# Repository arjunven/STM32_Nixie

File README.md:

# STM32 and USB-C Based Nixie Clock
A [Nixie](http://en.wikipedia.org/wiki/Nixie_tube) clock that's powered by USB-C and based on a STM32 microcontroller. Designed schematic, layout, and firmware from scratch! Fun mix of retro tech with modern electronics. Main Features:
  - Custom 5V to 180V boost converter that operates in discontinous conduction mode to power the Nixie tubes
  - USB-C Power input + bootloader
  - Push button dial that's used to set time and interface with the menu
  - Used high voltage shift registers to run the tube display
  - STM32F100 micro controller with abysmal flash storage ... because that's all that was in stock during the great covid parts shortage of 2021 when I started this project 

## Mostly Finished Product

  - Still would like to add a walnut enclosure and a nice wodden knob for the push button dial
  - 80/20 rule in full force

## Layout

- 4 Layer board

## Schematics
### 5V to 180V Boost Converter

### Full Schematics
[Full Schematics here
](https://github.com/arjunven/STM32_Nixie/blob/main/pcb/outputs/STM32_Nixie_Schematics.pdf
)

## Bringup/Development

- Bring up of HV shift register driver with assistance from Merlin

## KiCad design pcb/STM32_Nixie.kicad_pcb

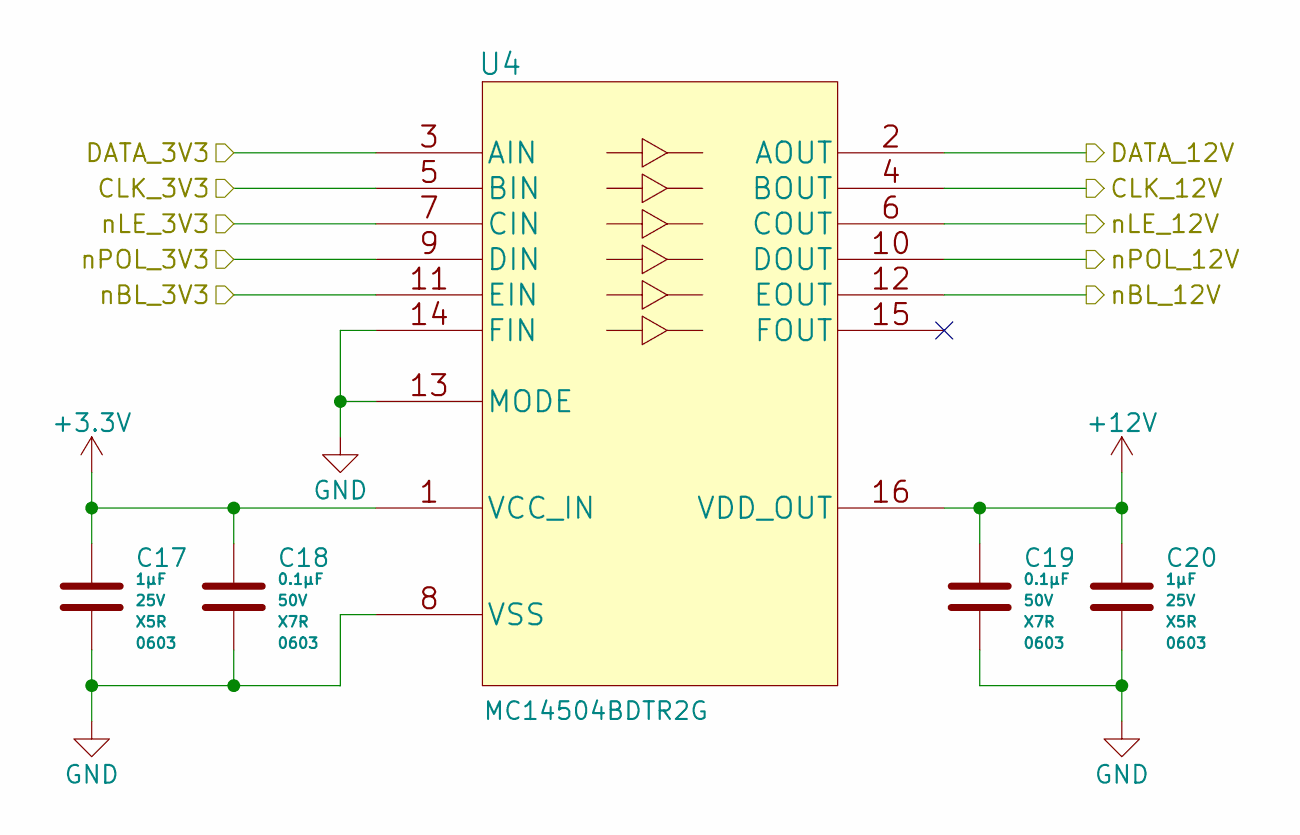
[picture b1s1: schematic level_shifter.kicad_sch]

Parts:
C17, C20: CAP_CER_1u_25V_X5R_0603; C_0603_1608Metric; Voltage 25V; ManufacturerPN CC0603KRX5R8BB105
C18, C19: CAP_CER_0u1_50V_X7R_0603; C_0603_1608Metric; Voltage 50V; ManufacturerPN CL10B104KB8NNNC
U4: IC_LVL_ONSEMI_MC14504BDTR2G; MC14504BDTR2G; ManufacturerPN MC14504BDTR2G

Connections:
+3.3V: C17.1, C18.1, U4.1 (VCC_IN); also elsewhere on the board
+12V: C19.1, C20.1, U4.16 (VDD_OUT); also elsewhere on the board
/PWM_nBL_3V3: U4.11 (EIN); also elsewhere on the board
/PWM_nBL_12V: U4.12 (EOUT); also elsewhere on the board
/SPI_PICO_3V3: U4.3 (AIN); also elsewhere on the board
/SPI_PICO_12V: U4.2 (AOUT); also elsewhere on the board
/SPI_SCK_3V3: U4.5 (BIN); also elsewhere on the board
/SPI_SCK_12V: U4.4 (BOUT); also elsewhere on the board
/SPI_nCS_nLE_3V3: U4.7 (CIN); also elsewhere on the board
/SPI_nCS_nLE_12V: U4.6 (COUT); also elsewhere on the board
/nPOL_3V3: U4.9 (DIN); also elsewhere on the board
/nPOL_12V: U4.10 (DOUT); also elsewhere on the board
GND: C17.2, C18.2, C19.2, C20.2, U4.8 (VSS), U4.13 (MODE), U4.14 (FIN); also elsewhere on the board

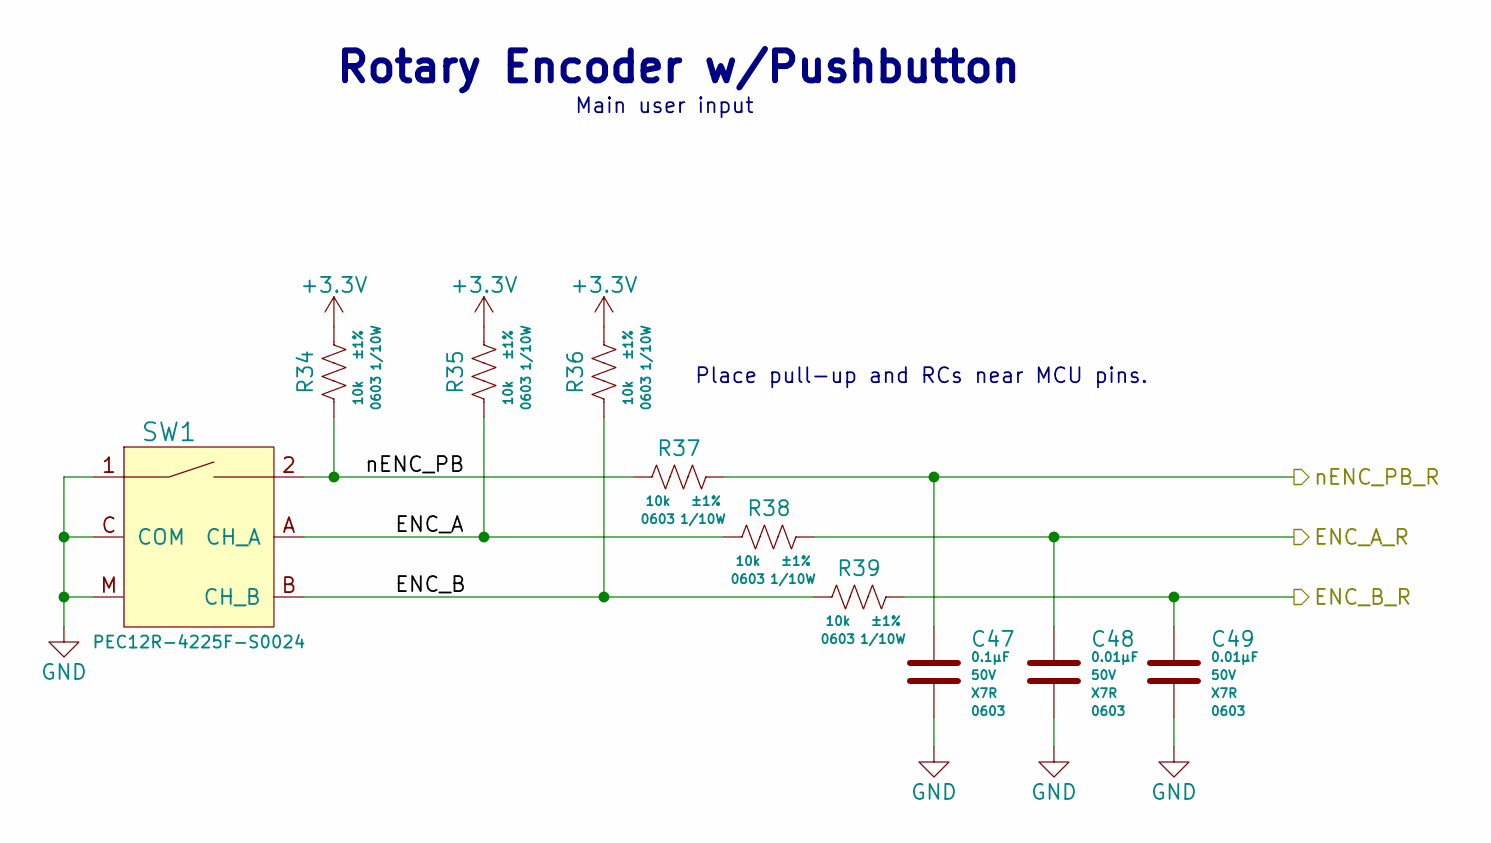
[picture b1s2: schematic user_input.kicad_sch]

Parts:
C47: CAP_CER_0u1_50V_X7R_0603; C_0603_1608Metric; Voltage 50V; ManufacturerPN CL10B104KB8NNNC
C48, C49: CAP_CER_0u01_50V_X7R_0603; C_0603_1608Metric; Voltage 50V; ManufacturerPN CL10B103KB8NNNC
R34, R35, R36, R37, R38, R39: RES_10K_1P_1/10W_0603; R_0603_1608Metric; Tolerance ±1%; ManufacturerPN RC0603FR-0710KL
SW1: ENC_SPST_24PPR_PEC12R-4225F-S0024; ENC_SPST_PEC12R-4x25F-Sxxx; ManufacturerPN PEC12R-4225F-S0024

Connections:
+3.3V: R34.1, R35.1, R36.1; also elsewhere on the board
/MCU/ENC_A_R: C48.1, R38.1; also elsewhere on the board
/MCU/ENC_B_R: C49.1, R39.1; also elsewhere on the board
/MCU/nENC_PB_R: C47.1, R37.1; also elsewhere on the board
/User Input/ENC_A: R35.2, R38.2, SW1.A (CH_A)
/User Input/ENC_B: R36.2, R39.2, SW1.B (CH_B)
/User Input/nENC_PB: R34.2, R37.2, SW1.2
GND: C47.2, C48.2, C49.2, SW1.1, SW1.C (COM), SW1.M; also elsewhere on the board

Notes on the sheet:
Place pull-up and RCs near MCU pins.
Rotary Encoder w/Pushbutton
Main user input

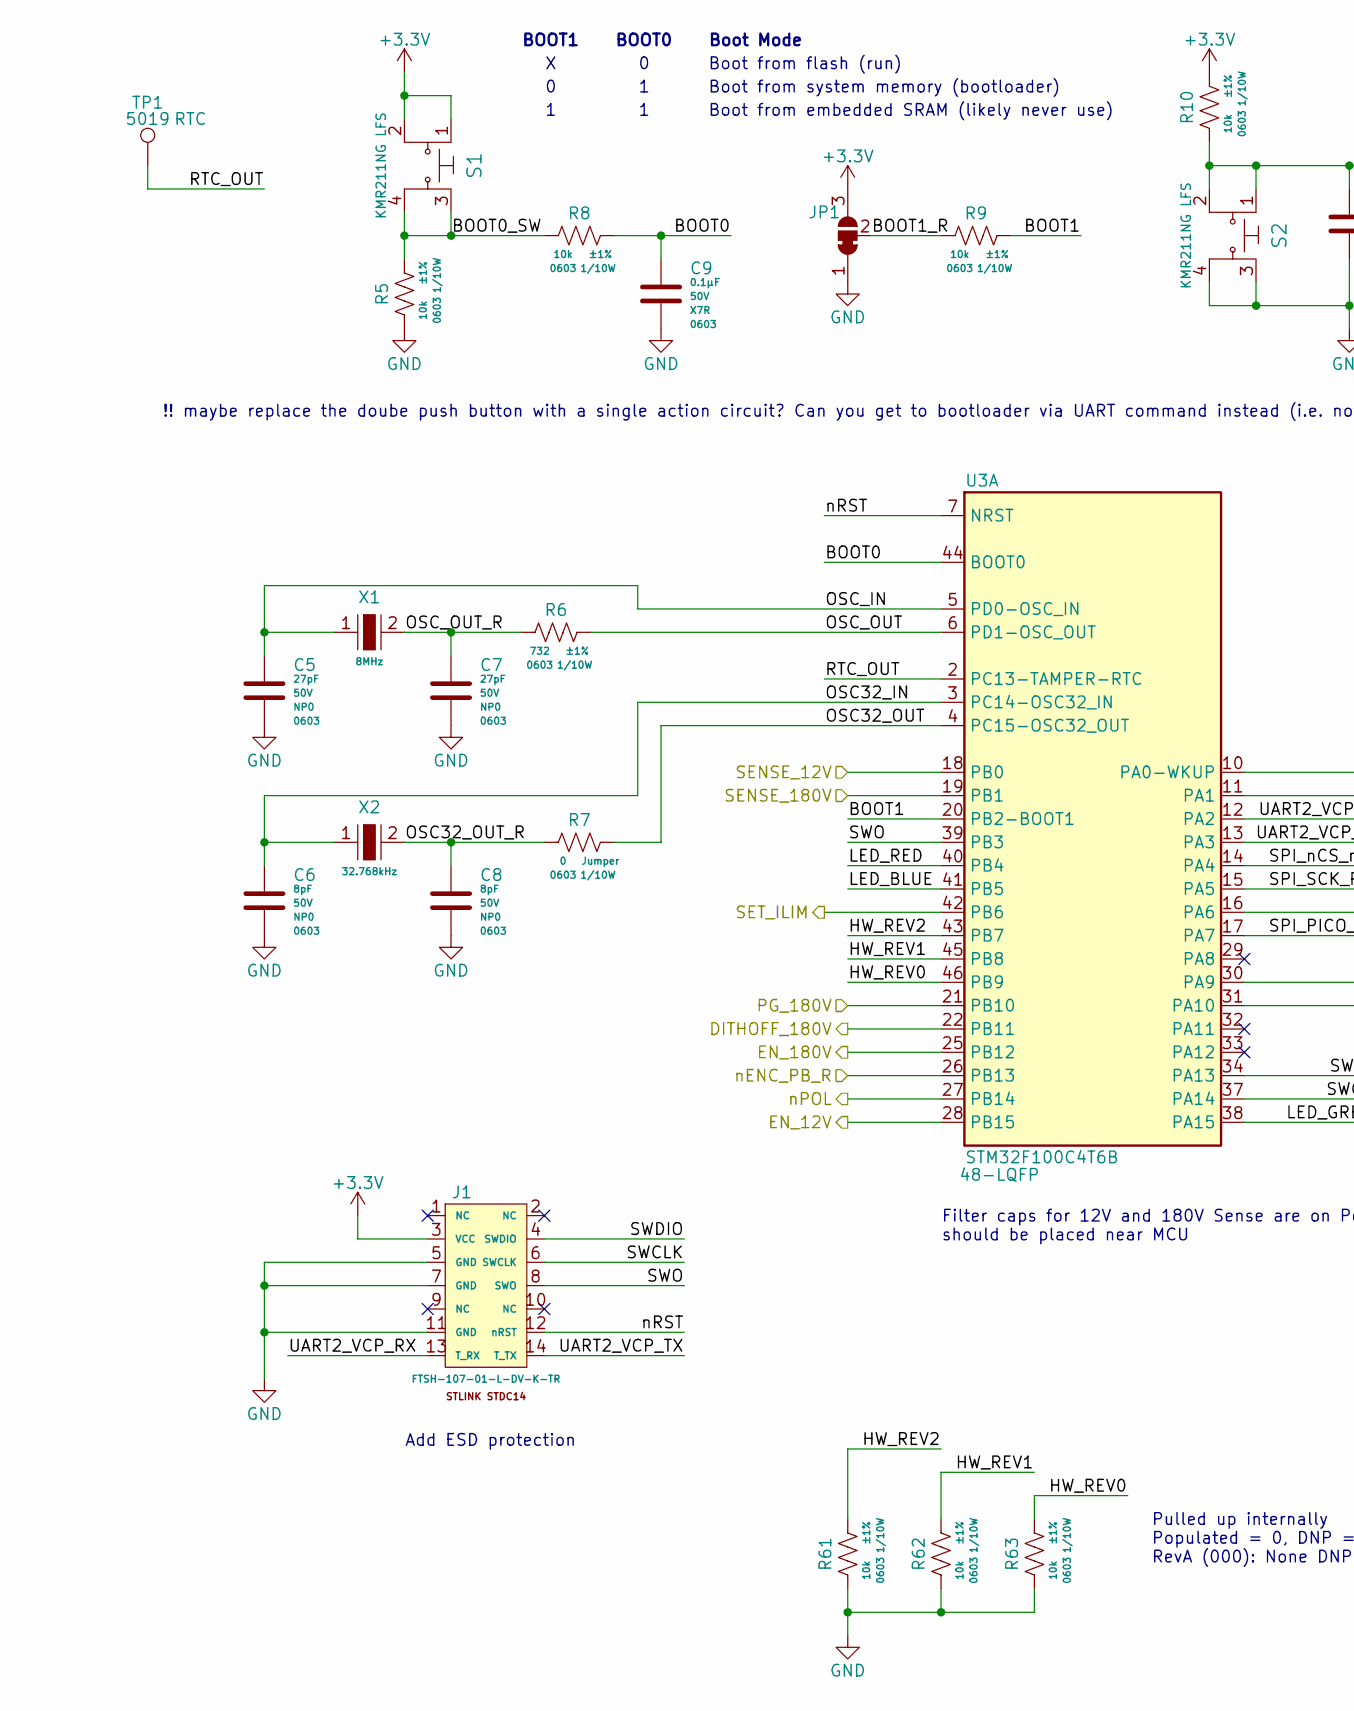
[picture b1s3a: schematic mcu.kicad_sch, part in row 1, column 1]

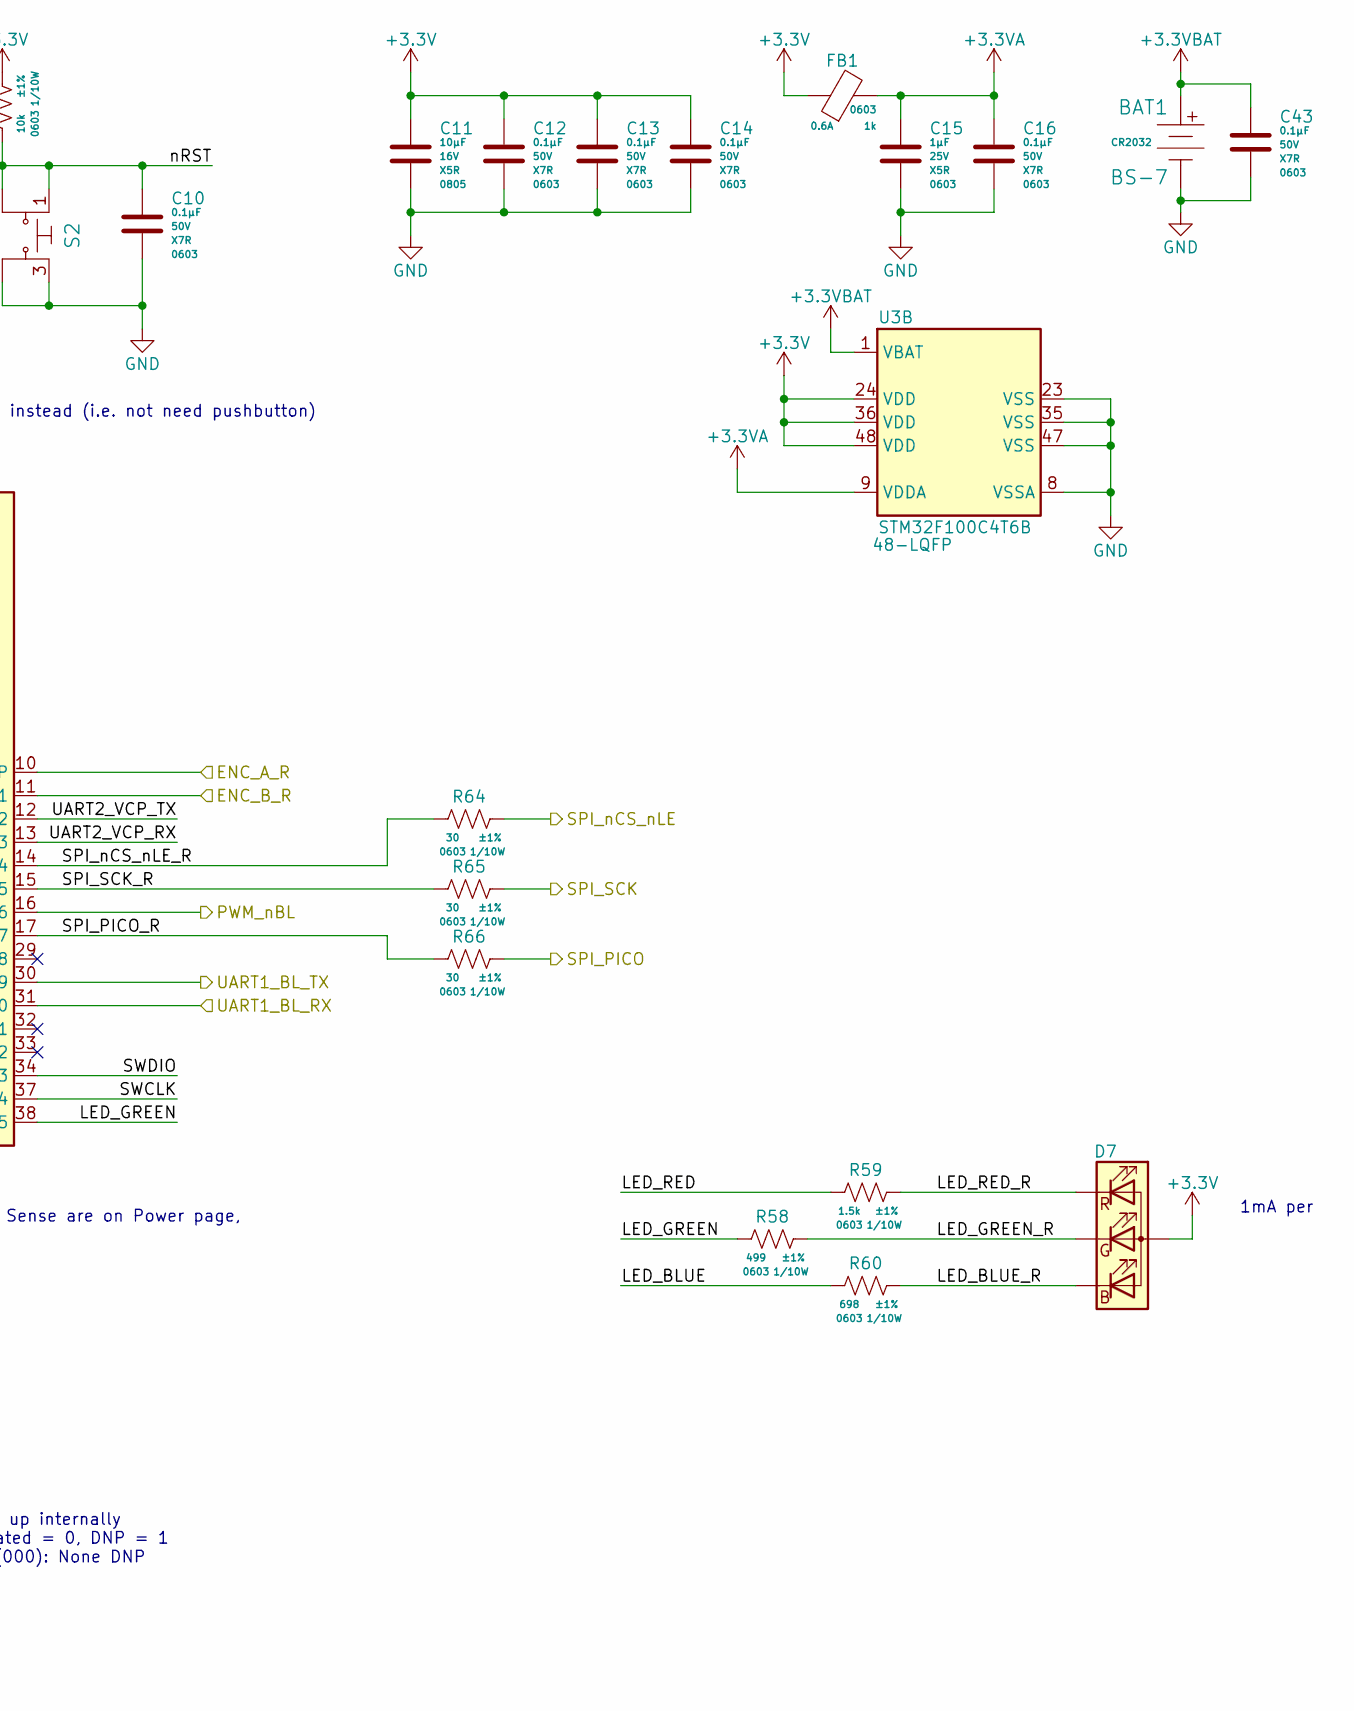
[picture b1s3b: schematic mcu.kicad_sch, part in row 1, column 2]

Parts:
BAT1: BS-7; Battery_Holder_Coin_2032_BS-7; ManufacturerPN BS-7
C5, C7: CAP_CER_27p_50V_NP0_0603; C_0603_1608Metric; Voltage 50V; ManufacturerPN CC0603FRNPO9BN270
C6, C8: CAP_CER_8p_50V_NP0_0603; C_0603_1608Metric; Voltage 50V; ManufacturerPN CBR06C809B5GAC
C9, C10, C12, C13, C14, C16, C43: CAP_CER_0u1_50V_X7R_0603; C_0603_1608Metric; Voltage 50V; ManufacturerPN CL10B104KB8NNNC
C11: CAP_CER_10u_16V_X5R_0805; C_0805_2012Metric; Voltage 16V; ManufacturerPN CL21A106KOQNNNE
C15: CAP_CER_1u_25V_X5R_0603; C_0603_1608Metric; Voltage 25V; ManufacturerPN CC0603KRX5R8BB105
D7: LED_RGB_0606; EAST1616RGBB2_EVE; ManufacturerPN EAST1616RGBB2
FB1: FER_1K_0A6_0603; L_0603_1608Metric; ManufacturerPN 742792662
J1: CON_SAMTEC_14P_2R_1m27_P_KEY_FTSH-107-01-L-DV-K-TR; CON_FTSH-107-01-x-DV-K; ManufacturerPN FTSH-107-01-L-DV-K-TR
JP1: SolderJumper_3_Bridged12; SolderJumper-3_P1.3mm_Bridged12_RoundedPad1.0x1.5mm_NumberL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
R5, R8, R9, R10, R61, R62, R63: RES_10K_1P_1/10W_0603; R_0603_1608Metric; Tolerance ±1%; ManufacturerPN RC0603FR-0710KL
R6: RES_732R_1P_1/10W_0603; R_0603_1608Metric; Tolerance ±1%; ManufacturerPN RC0603FR-07732RL
R7: RES_0R_1/10W_0603; R_0603_1608Metric; Tolerance Jumper; ManufacturerPN RMCF0603ZT0R00
R58: RES_499R_1P_1/10W_0603; R_0603_1608Metric; Tolerance ±1%; ManufacturerPN RC0603FR-07499RL
R59: RES_1K5_1P_1/10W_0603; R_0603_1608Metric; Tolerance ±1%; ManufacturerPN RC0603FR-071K5L
R60: RES_698R_1P_1/10W_0603; R_0603_1608Metric; Tolerance ±1%; ManufacturerPN RC0603FR-07698RL
R64, R65, R66: RES_30R_1P_1/10W_0603; R_0603_1608Metric; Tolerance ±1%; ManufacturerPN RC0603FR-0730RL
S1, S2: SW_TACT_KMR211NG LFS; SW_Push_1P1T_NO_CK_KMR2; ManufacturerPN KMR211NG LFS
TP1: RTC; TestPoint_Keystone_5019_Minature; ManufacturerPN 5019
U3: IC_MCU_STM32F100C4T6B_48LQFP; LQFP-48_7x7mm_P0.5mm; ManufacturerPN STM32F100C4T6B
X1: XTAL_8M_20PPM_18pF_ECS-80-18-30-JGN-TR; SMD-2_5x3.2mm_ECS; Frequency Tolerance 20ppm; ManufacturerPN ECS-80-18-30-JGN-TR
X2: XTAL_32K768_10PPM_7pF_ECS-.327-7-34B-C-TR; SMD-2_3.2x1.5mm_ECS; Frequency Tolerance 10ppm; ManufacturerPN ECS-.327-7-34B-C-TR

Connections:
+3.3V: C11.1, C12.1, C13.1, C14.1, D7.4 (A), FB1.1, J1.3 (VCC), JP1.3 (B), R10.1, S1.1, S1.2, U3.24 (VDD), U3.36 (VDD), U3.48 (VDD); also elsewhere on the board
+3.3VA: C15.1, C16.1, FB1.2, U3.9 (VDDA)
+3.3VBAT: BAT1.Pos, C43.1, U3.1 (VBAT)
/MCU/BOOT0: C9.1, R8.1, U3.44 (BOOT0)
/MCU/BOOT0_SW: R5.1, R8.2, S1.3, S1.4
/MCU/BOOT1: R9.1, U3.20 (PB2-BOOT1)
/MCU/BOOT1_R: JP1.2 (C), R9.2
/MCU/DITHOFF_180V: U3.22 (PB11); also elsewhere on the board
/MCU/ENC_A_R: U3.10 (PA0-WKUP); also elsewhere on the board
/MCU/ENC_B_R: U3.11 (PA1); also elsewhere on the board
/MCU/EN_12V: U3.28 (PB15); also elsewhere on the board
/MCU/EN_180V: U3.25 (PB12); also elsewhere on the board
/MCU/HW_REV0: R63.1, U3.46 (PB9)
/MCU/HW_REV1: R62.1, U3.45 (PB8)
/MCU/HW_REV2: R61.1, U3.43 (PB7)
/MCU/LED_BLUE: R60.2, U3.41 (PB5)
/MCU/LED_BLUE_R: D7.3 (BK), R60.1
/MCU/LED_GREEN: R58.2, U3.38 (PA15)
/MCU/LED_GREEN_R: D7.2 (GK), R58.1
/MCU/LED_RED: R59.2, U3.40 (PB4)
/MCU/LED_RED_R: D7.1 (RK), R59.1
/MCU/OSC32_IN: C6.1, U3.3 (PC14-OSC32_IN), X2.1
/MCU/OSC32_OUT: R7.1, U3.4 (PC15-OSC32_OUT)
/MCU/OSC32_OUT_R: C8.1, R7.2, X2.2
/MCU/OSC_IN: C5.1, U3.5 (PD0-OSC_IN), X1.1
/MCU/OSC_OUT: R6.1, U3.6 (PD1-OSC_OUT)
/MCU/OSC_OUT_R: C7.1, R6.2, X1.2
/MCU/PG_180V: U3.21 (PB10); also elsewhere on the board
/MCU/RTC_OUT: TP1.1, U3.2 (PC13-TAMPER-RTC)
/MCU/SENSE_12V: U3.18 (PB0); also elsewhere on the board
/MCU/SENSE_180V: U3.19 (PB1); also elsewhere on the board
/MCU/SET_ILIM: U3.42 (PB6); also elsewhere on the board
/MCU/SPI_PICO_R: R66.2, U3.17 (PA7)
/MCU/SPI_SCK_R: R65.2, U3.15 (PA5)
/MCU/SPI_nCS_nLE_R: R64.2, U3.14 (PA4)
/MCU/SWCLK: J1.6 (SWCLK), U3.37 (PA14)
/MCU/SWDIO: J1.4 (SWDIO), U3.34 (PA13)
/MCU/SWO: J1.8 (SWO), U3.39 (PB3)
/MCU/UART1_BL_RX: U3.31 (PA10); also elsewhere on the board
/MCU/UART1_BL_TX: U3.30 (PA9); also elsewhere on the board
/MCU/UART2_VCP_RX: J1.13 (T_RX), U3.13 (PA3)
/MCU/UART2_VCP_TX: J1.14 (T_TX), U3.12 (PA2)
/MCU/nENC_PB_R: U3.26 (PB13); also elsewhere on the board
/MCU/nRST: C10.1, J1.12 (nRST), R10.2, S2.1, S2.2, U3.7 (NRST)
/PWM_nBL_3V3: U3.16 (PA6); also elsewhere on the board
/SPI_PICO_3V3: R66.1; also elsewhere on the board
/SPI_SCK_3V3: R65.1; also elsewhere on the board
/SPI_nCS_nLE_3V3: R64.1; also elsewhere on the board
/nPOL_3V3: U3.27 (PB14); also elsewhere on the board
GND: BAT1.Neg, C5.2, C6.2, C7.2, C8.2, C9.2, C10.2, C11.2, C12.2, C13.2, C14.2, C15.2, C16.2, C43.2, J1.5 (GND), J1.7 (GND), J1.11 (GND), JP1.1 (A), R5.2, R61.2, R62.2, R63.2, S2.3, S2.4, U3.8 (VSSA), U3.23 (VSS), U3.35 (VSS), U3.47 (VSS); also elsewhere on the board

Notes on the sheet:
Boot from flash (run)
!! maybe replace the doube push button with a single action circuit? Can you get to bootloader via UART command instead (i.e. not need pushbutton)
Boot from system memory (bootloader)
1mA per
Add ESD protection
Filter caps for 12V and 180V Sense are on Power page, should be placed near MCU
Boot Mode
BOOT1
Pulled up internally Populated = 0, DNP = 1 RevA (000): None DNP
BOOT0
Boot from embedded SRAM (likely never use)
